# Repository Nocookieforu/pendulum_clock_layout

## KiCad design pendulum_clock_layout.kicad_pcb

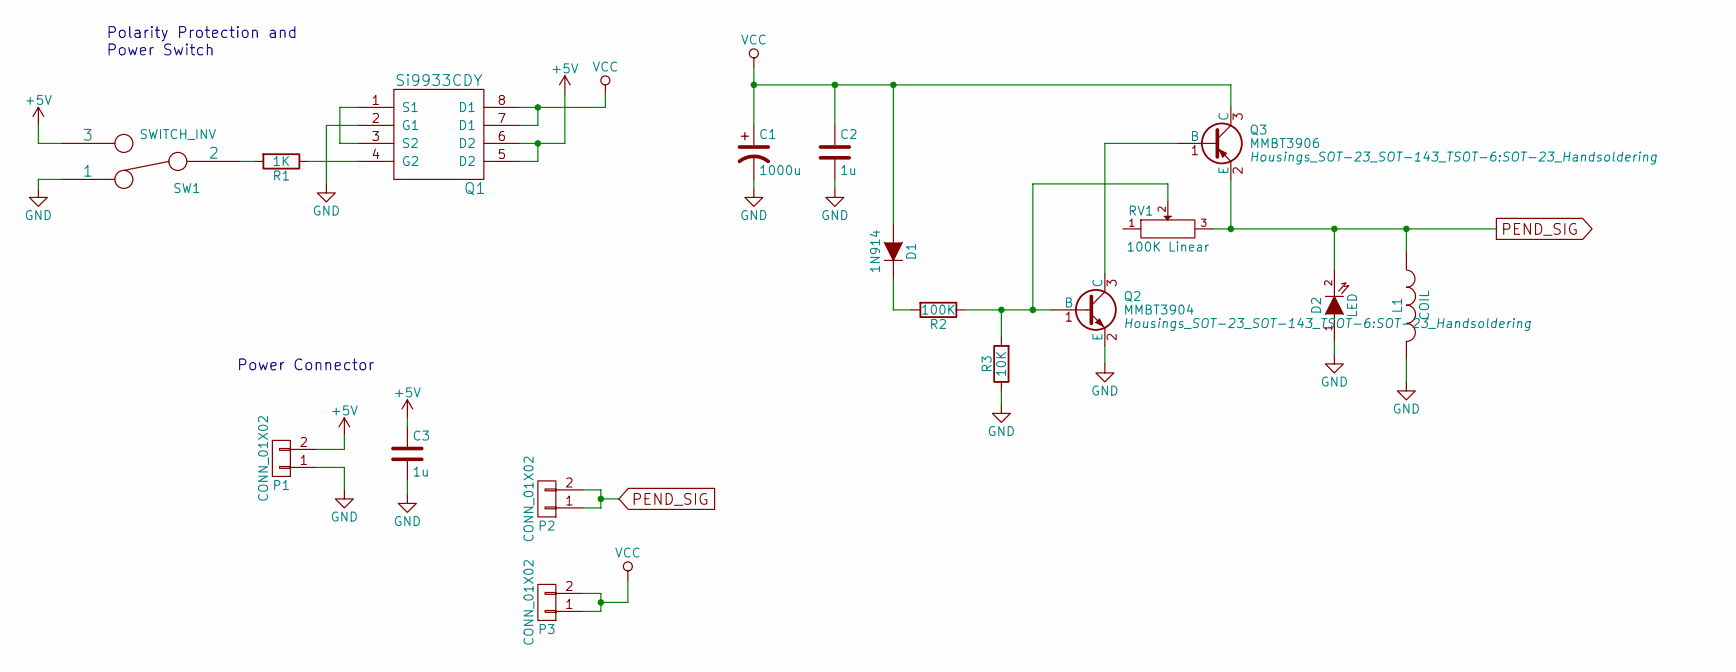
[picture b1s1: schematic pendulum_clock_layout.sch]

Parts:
C1: 1000u; Elko_vert_11x5mm_RM2.5
C2, C3: 1u; C_0603_HandSoldering
D1: 1N914; SOT-23_Handsoldering
D2: LED; LED-5MM
L1: COIL; Pin_Header_Straight_1x02
P1, P2, P3: CONN_01X02; Pin_Header_Straight_1x02
Q1: Si9933CDY; SOIC-8_3.9x4.9mm_Pitch1.27mm
Q2: MMBT3904; SOT-23_Handsoldering
Q3: MMBT3906; SOT-23_Handsoldering
R1: 1K; R_0603_HandSoldering
R2: 100K; R_0603_HandSoldering
R3: 10K; R_0603_HandSoldering
RV1: 100K Linear; Pin_Header_Straight_1x03
SW1: SWITCH_INV; Pin_Header_Straight_1x03

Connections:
+5V: C3.1, P1.2, Q1.5 (D2), Q1.6 (D2), SW1.3
GND: C1.2, C2.2, C3.2, D2.1 (A), L1.2, P1.1, Q1.2 (G1), Q2.2 (E), R3.1, SW1.1
unnamed: D1.2 (K), R2.2
unnamed: Q1.1 (S1), Q1.3 (S2)
unnamed: Q1.4 (G2), R1.1
unnamed: Q2.1 (B), R2.1, R3.2, RV1.2
unnamed: Q2.3 (C), Q3.1 (B)
unnamed: R1.2, SW1.2
PEND_SIG: D2.2 (K), L1.1, P2.1, P2.2, Q3.2 (E), RV1.3
VCC: C1.1, C2.1, D1.1 (A), P3.1, P3.2, Q1.7 (D1), Q1.8 (D1), Q3.3 (C)

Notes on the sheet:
Polarity Protection and Power Switch
Power Connector

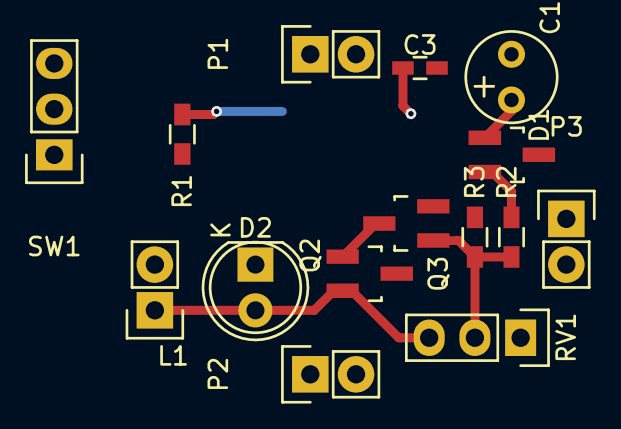
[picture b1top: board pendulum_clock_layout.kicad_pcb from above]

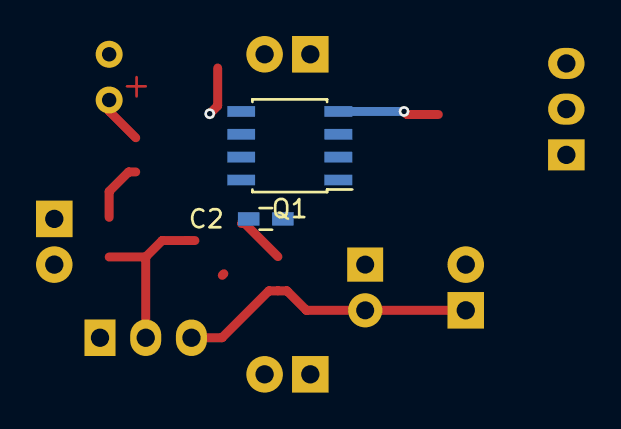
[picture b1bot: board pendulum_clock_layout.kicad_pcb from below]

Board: 2 copper layers, 17 parts (2 on the bottom side), 10 nets.

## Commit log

2015-12-13 Added all files
